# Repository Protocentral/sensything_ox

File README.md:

Protocentral Sensything Ox Wireless Pulse Sensor Kit based on AFE4400/ESP32S3
========================================

## Don't have one? [Buy it here](https://protocentral.com/product/protocentral-sensythingox-wireless-pulse-sensor-kit-based-on-afe4400-esp32/)

Protocentral Sensything Ox is the latest, renamed version of our popular [OpenOx](https://github.com/Protocentral/protocentral_openox) Pulse sensor board. It is a standalone, wireless pulse oximetry breakout board that is powered by the ESP32S3 module and uses the AFE4400 IC to measure oxygen levels in the blood while also providing a PPG waveform, heart rate, and SpO2 values measured with high precision.

The Sensything Ox improves upon the previous version of the [OpenOx board](https://github.com/Protocentral/protocentral_openox) by replacing the ESP32 module with the new ESP32S3 with 8MB Flash memory and 2MB PSRAM. This allows for a more powerful and efficient processing of the data collected by the AFE4400 IC. The board is designed to be used in a variety of applications, including medical research, fitness tracking, and remote patient monitoring.

## Hardware Setup

The Sensything Ox programs are all in Arduino and examples are in the examples folder of this repo. To program, select the "ESP32S3 Dev Module" board in the Arduino IDE with the following settings.

* Board: ESP32S3 Dev Module
* USB Mode: Hardware CDC and JTAG
* USB CDC on Boot: Enabled
* Upload Mode: UART0 / Hardware CDC
* PSRAM: QSPI PSRAM

# Documentation

For further details of the board, refer the documentation at the following links:

[Protocentral Sensything Ox Wireless Pulse Sensor Documentation](https://docs.protocentral.com/getting-started-with-openox/)

# Visualizing Output

### USB Streaming

* Open the GUI, make sure to select **AFE4490 breakout** under the **Board** dropdown and the appropriate **Port**. If everything goes well, you will be able to see the screen as pictured above.

   <center>

  </center>

### BLE streaming

 <center>

  </center>

 <center>

  </center>

License Information
===================

This product is open source! Both, our hardware and software are open source and licensed under the following licenses:

Hardware
---------

**All hardware is released under the [CERN-OHL-P v2](https://ohwr.org/cern_ohl_p_v2.txt)** license.

Copyright CERN 2020.

This source describes Open Hardware and is licensed under the CERN-OHL-P v2.

You may redistribute and modify this documentation and make products
using it under the terms of the CERN-OHL-P v2 (https:/cern.ch/cern-ohl).
This documentation is distributed WITHOUT ANY EXPRESS OR IMPLIED
WARRANTY, INCLUDING OF MERCHANTABILITY, SATISFACTORY QUALITY
AND FITNESS FOR A PARTICULAR PURPOSE. Please see the CERN-OHL-P v2
for applicable conditions

Software
--------

**All software is released under the MIT License(http://opensource.org/licenses/MIT).**

THE SOFTWARE IS PROVIDED "AS IS", WITHOUT WARRANTY OF ANY KIND, EXPRESS OR IMPLIED, INCLUDING BUT NOT LIMITED TO THE WARRANTIES OF MERCHANTABILITY, FITNESS FOR A PARTICULAR PURPOSE AND NONINFRINGEMENT. IN NO EVENT SHALL THE AUTHORS OR COPYRIGHT HOLDERS BE LIABLE FOR ANY CLAIM, DAMAGES OR OTHER LIABILITY, WHETHER IN AN ACTION OF CONTRACT, TORT OR OTHERWISE, ARISING FROM, OUT OF OR IN CONNECTION WITH THE SOFTWARE OR THE USE OR OTHER DEALINGS IN THE SOFTWARE.

Documentation
-------------
**All documentation is released under [Creative Commons Share-alike 4.0 International](http://creativecommons.org/licenses/by-sa/4.0/).**

You are free to:

* Share — copy and redistribute the material in any medium or format
* Adapt — remix, transform, and build upon the material for any purpose, even commercially.
The licensor cannot revoke these freedoms as long as you follow the license terms.

Under the following terms:

* Attribution — You must give appropriate credit, provide a link to the license, and indicate if changes were made. You may do so in any reasonable manner, but not in any way that suggests the licensor endorses you or your use.
* ShareAlike — If you remix, transform, or build upon the material, you must distribute your contributions under the same license as the original.

Please check [*LICENSE.md*](LICENSE.md) for detailed license descriptions.

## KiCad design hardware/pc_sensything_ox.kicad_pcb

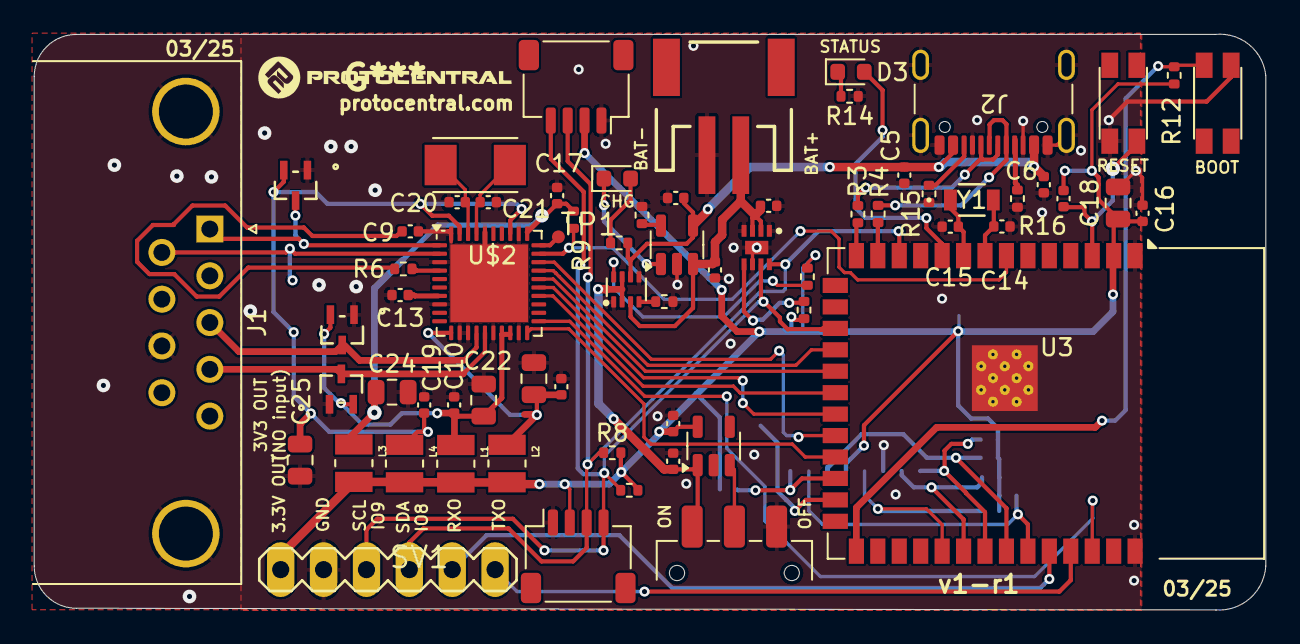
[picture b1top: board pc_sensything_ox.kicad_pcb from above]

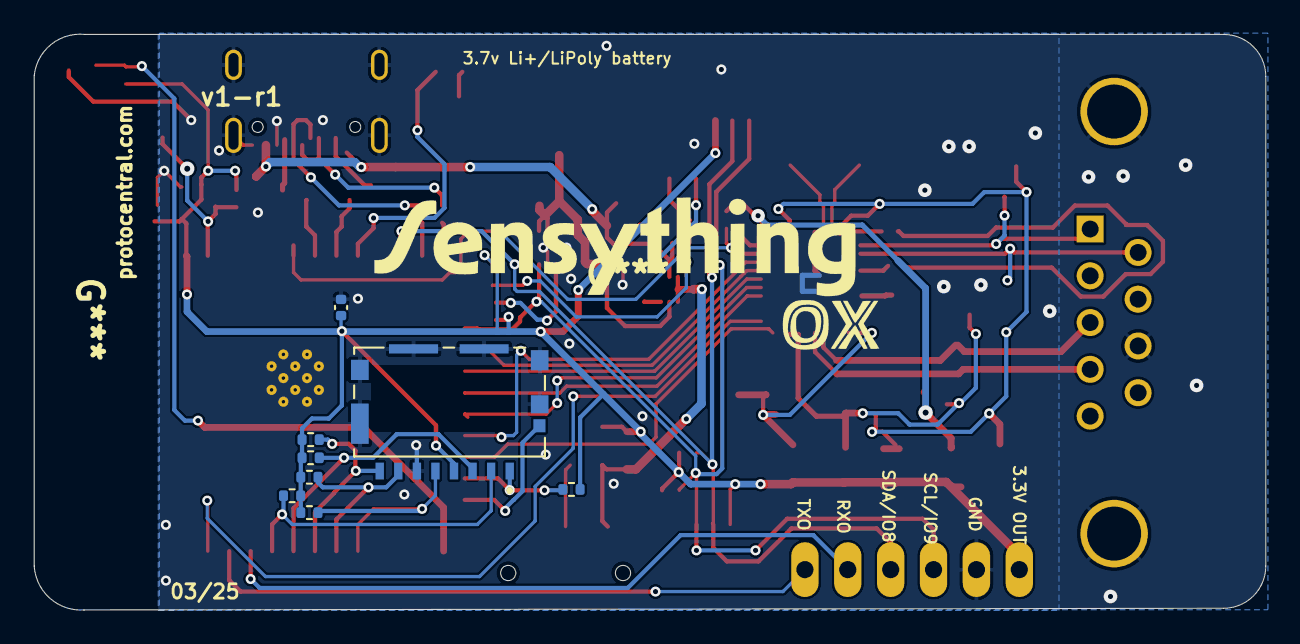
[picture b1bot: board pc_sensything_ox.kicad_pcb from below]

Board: 2 copper layers, 73.0 x 34.1 mm, 74 parts (8 on the bottom side), 57 nets.

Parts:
C5: 4.7uF; C_0402_1005Metric
C6: 100nF; C_0402_1005Metric
C8, C10, C11: 1u; C_0402_1005Metric
C9, C13: 2.2u; C_0402_1005Metric
C12, C17, C19: 0.1u; C_0402_1005Metric
C14, C15: 12pF; C_0402_1005Metric
C16: 100n; C_0402_1005Metric
C18, C22, C23, C24, C25: 10uF; C_0805_2012Metric
C20, C21: 22p; C_0402_1005Metric
C29: 1uF; C_0402_1005Metric
C45, C46: 2.2uF; C_0402_1005Metric
C50: 0.1uF; C_0402_1005Metric
D3: LED; LED_0603_1608Metric
D4: Red; LED_0603_1608Metric
D5, D6, D7: D_ACACSOT323; SOT-323_DIO
J1: DE9_Socket_MountingHoles; DSUB-9_Pins_Horizontal_P2.77x2.84mm_EdgePinOffset7.70mm_Hou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
J2: USB_C_Receptacle_USB2.0_16P; USB_C_Receptacle_GCT_USB4105-xx-A_16P_TopMnt_Horizontal
J3, J6: Qwiic2; JST_SH_SM04B-SRSS-TB_1x04-1MP_P1.00mm_Horizontal
J5: JST_2mm_LiPo; JST_SMD_2.0mm-2
J7: 1051620001; MOLEX_1051620001
L1, L2, L3, L4: MAKK2520H100M; INDC2520X100N
R3, R4, R6, R9: 0R; R_0402_1005Metric
R7, R8: 10K; R_0402_1005Metric
R12, R17, R18, R19, R20, R35: 10k; R_0402_1005Metric
R13: 10k; C_0402_1005Metric
R14: 330R; R_0402_1005Metric
R15, R16: 5.1K; R_0402_1005Metric
R21, R22: DNP; R_0402_1005Metric
R31: 4.7k; R_0402_1005Metric
R32: 2.2k; R_0402_1005Metric
R33, R34: 100k; R_0402_1005Metric
SV1: MA06-1
SW1, SW2: KMR2; BTN_KMR2_4.6X2.8
SW3: SW_SPDT; SW_SPDT_CK_JS102011SAQN
TP1: TEST-POINT3; PAD.03X.03
U1: MAX17048; DFN-8
U2: LM66200; SOT-583-8
U3: ESP32-S3-WROOM-1
U5: AP2112K-3.3; SOT-23-5
U10: MCP73831; SOT-23-5
U$2: AFE4400; Texas_RHA_VQFN-40-1EP_6x6mm_P0.5mm_EP4.6x4.6mm
U$3: ABM3; XTAL_ABM3-8.000MHZ-B4Y-T
Y1: ECS-.327-12.5-34B; XTAL_ECS-31B_ECS-L

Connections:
0: R12.1, SW1.A, U3.27 (IO0)
+3V3: C11.2, C16.1, C18.1, C29.1, J3.2, J6.2, J7.P4 (VDD), L1.2, L2.2, L3.2, L4.2, R7.2, R8.2, R12.2, R13.2, R17.1, R18.1, R19.1, R20.1, R21.1, R22.1, R34.1, R35.1, SV1.1, U3.2 (3V3), U5.5 (VOUT)
/INN: D7.1 (CA), J1.1, U$2.1 (INN)
/INP: J1.6, U$2.2 (INP)
/LED_DRV_SUP: C10.1, C22.1, D5.3 (A), D6.3 (A), L1.1, U$2.17 (LED_DRV_SUP@1), U$2.18 (LED_DRV_SUP@2)
/RX_ANA_SUP: C19.1, C25.1, D7.3 (A), L4.1, U$2.33 (RX_ANA_SUP), U$2.39 (RX_ANA_SUP@1)
/RX_DIG_SUP: C17.1, C24.1, L3.1, R9.1, U$2.31 (RX_DIG_SUP@3)
/TXP: D6.1 (CA), J1.4, U$2.15 (TXP)
/TX_CTRL_SUP: C12.1, C23.1, L2.1, U$2.11 (TX_CTRL_SUP)
/VCM: R6.1, U$2.4 (VCM)
ADC_RDY: U3.22 (IO14), U$2.28 (ADC_RDY)
BAT_POWER: R34.2, U2.8 (ST)
CHIP_PU: R13.1, SW2.A, U3.3 (EN)
DIAG_END: U3.38 (IO2), U$2.21 (DIAG_END)
FUEL_GAUGE_~ALRT: R35.2, U1.5 (~ALRT)
GND: C5.2, C6.2, C8.1, C9.2, C10.2, C11.1, C12.2, C13.2, C14.1, C15.2, C16.2, C17.2, C18.2, C19.2, C20.1, C21.1, C22.2, C23.2, C24.2, C25.2, C29.2, C45.2, C46.2, C50.2, D5.2 (C), D6.2 (C), D7.2 (C), J1.0 (PAD), J1.8, J2.A1 (GND), J2.A8 (SBU1), J2.A12 (GND), J2.B1 (GND), J2.B8 (SBU2), J2.B12 (GND), J2.S1 (SHIELD), J3.1, J5.1 (-), J6.1, J7.G1 (GND), J7.G2 (GND__1), J7.G3 (GND__2), J7.G4 (GND__3), J7.P6 (VSS), J7.SH1 (SHIELD), J7.SH2 (SHIELD__1), R14.1, R15.1, R16.1, R32.2, R33.2, SV1.2, SW1.B (S), SW2.B (S), SW3.3 (C), U1.1 (CTG), U1.4 (GND), U1.6 (QSTRT), U1.9 (GND), U2.1 (GND), U2.5 (GND), U3.1 (GND), U3.40 (GND), U3.41 (GND), U5.2 (GND), U10.2 (GND), U$2.3 (RX_ANA_GND), U$2.8 (VSS), U$2.12 (LED_DRV_GND@1), U$2.13 (LED_DRV_GND@2), U$2.16 (LED_DRV_GND@3), U$2.19 (RX_DIG_GND), U$2.32 (RX_DIG_GND@1), U$2.36 (RX_ANA_GND@1), U$2.40 (RX_ANA_GND@2), U$2.41 (EPAD)
LED1: D3.2 (A), U3.10 (IO17)
unnamed: C9.1, R6.2
unnamed: D3.1 (K), R14.2
unnamed: D4.2 (A), R31.2
unnamed: D4.1 (K), U10.1 (STAT)
unnamed: D5.1 (CA), J1.3, U$2.14 (TXN)
unnamed: J2.A5 (CC1), R16.2
unnamed: J2.B5 (CC2), R15.2
unnamed: J2.A6 (D+), J2.B6 (D+), R3.1
unnamed: J2.A7 (D-), J2.B7 (D-), R4.1
unnamed: TP1.P$1 (1), U$2.30 (CLKOUT)
unnamed: R33.1, U2.4 (~ON)
unnamed: C14.2, U3.8 (IO15), Y1.2
unnamed: C15.1, U3.9 (IO16), Y1.1
unnamed: R32.1, U10.5 (PROG)
unnamed: C13.1, U$2.7 (BG)
unnamed: C20.2, U$2.38 (XIN), U$3.2
unnamed: C21.2, U$2.37 (XOUT), U$3.1
PWR_ON: SW3.2 (B), U5.3 (EN)
SCL: J3.4, J6.4, R7.1, SV1.3, U1.7 (SCL), U3.17 (IO9)
SDA: J3.3, J6.3, R8.1, SV1.4, U1.8 (SDA), U3.12 (IO8)
SDMMC1_CK: J7.P5 (CLK), R21.2, U3.31 (IO38)
SDMMC1_CMD: J7.P3 (CMD), R22.2, U3.34 (IO41)
SDMMC1_D0: J7.P7 (DAT0), R17.2, U3.32 (IO39)
SDMMC1_D1: J7.P8 (DAT1), R18.2, U3.33 (IO40)
SDMMC1_D2: J7.P1 (DAT2), R20.2, U3.24 (IO47)
SDMMC1_D3: J7.P2 (CD/DAT3), R19.2, U3.35 (IO42)
SD_DETECT: J7.P9 (DET), U3.25 (IO48)
SPO2_CS0: U3.18 (IO10), U$2.27 (SPISTE)
SPO2_MISO: U3.21 (IO13), U$2.25 (SPISOMI)
SPO2_MOSI: U3.19 (IO11), U$2.26 (SPISIMO)
SPO2_SCK: U3.20 (IO12), U$2.24 (SCLK)
UART_RX: SV1.5, U3.36 (RXD0)
UART_TX: SV1.6, U3.37 (TXD0)
USB_D+: R3.2, U3.14 (USB_D+)
USB_D-: R4.2, U3.13 (USB_D-)
VBATT: C46.1, C50.1, J5.2 (+), U1.2 (CELL), U1.3 (VDD), U2.3 (VIN1), U10.3 (V_{BAT})
VS: C8.2, SW3.1 (A), U2.2 (VOUT), U2.7 (VOUT), U5.1 (VIN)
VUSB: C5.1, C6.1, C45.1, J2.A4 (VBUS), J2.A9 (VBUS), J2.B4 (VBUS), J2.B9 (VBUS), R31.1, U2.6 (VIN2), U10.4 (VIN)
~ADC_RESET: R9.2, U3.7 (IO7), U$2.29 (~RESET)
~AFE_PDN: U3.23 (IO21), U$2.20 (AFE_~PDN)

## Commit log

2025-04-04 Added initial code
2025-04-19 Updated Sensything Ox board
2025-04-19 Updated OpenOx reference
2025-04-21 For update
2025-04-29 Minor corrections

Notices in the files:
README.md:
CC-BY-SA-4.0
